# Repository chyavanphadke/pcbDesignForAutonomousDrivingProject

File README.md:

# pcbDesignForAutonomousDrivingProject

Schematic Diagram

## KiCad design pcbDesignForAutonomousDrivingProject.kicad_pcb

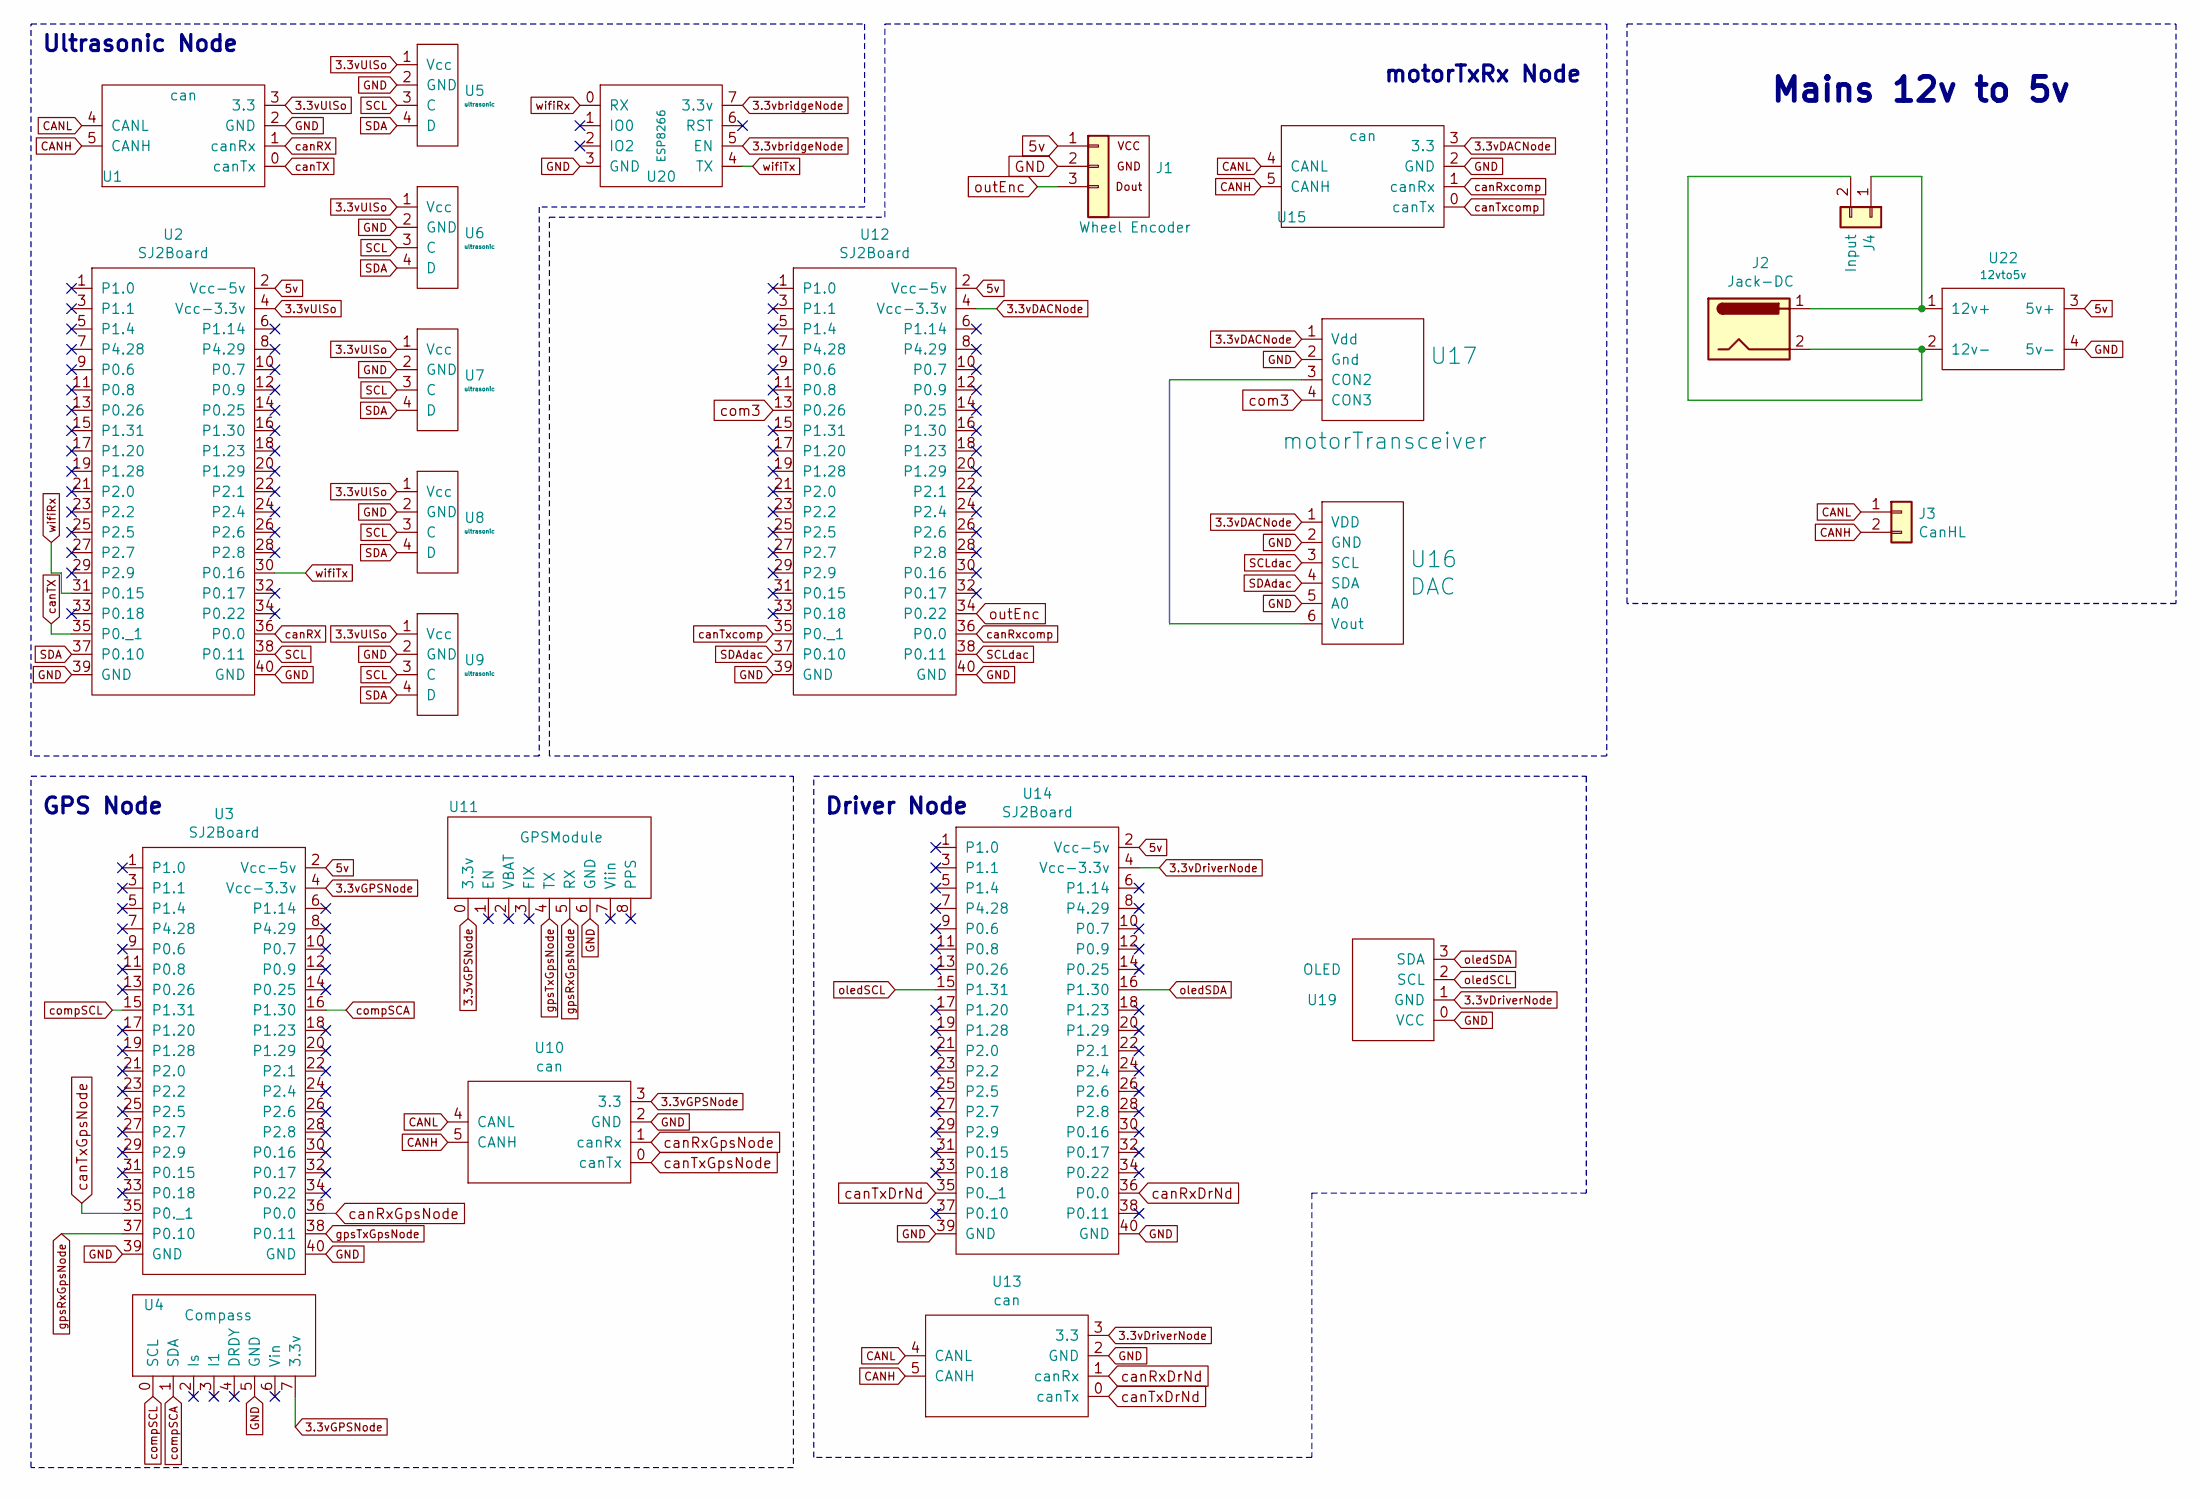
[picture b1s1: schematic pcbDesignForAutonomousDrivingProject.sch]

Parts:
J1: Wheel Encoder; WheelEncoder
J2: Jack-DC; BarrelJack_Horizontal
J3: CanHL; PinHeader_1x02_P2.54mm_Vertical
J4: Input; PinHeader_1x02_P2.54mm_Vertical
U1, U10, U13, U15: can
U2, U3, U12, U14: SJ2Board; sj2Board
U4: Compass; compass
U5, U6, U7, U8, U9: ultrasonic
U11: GPSModule; GPS
U16: DAC
U17: motorTransceiver
U19: OLED; Oled
U20: ESP8266
U22: 12vto5v

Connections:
3.3vDACNode: U12.4 (Vcc-3.3v), U15.3 (3.3), U16.1 (VDD), U17.1 (Vdd)
3.3vDriverNode: U13.3 (3.3), U14.4 (Vcc-3.3v), U19.1 (GND)
3.3vGPSNode: U3.4 (Vcc-3.3v), U4.7 (3.3v), U10.3 (3.3), U11.0 (3.3v)
3.3vUlSo: U1.3 (3.3), U2.4 (Vcc-3.3v), U5.1 (Vcc), U6.1 (Vcc), U7.1 (Vcc), U8.1 (Vcc), U9.1 (Vcc)
3.3vbridgeNode: U20.5 (EN), U20.7 (3.3v)
5v: J1.1 (VCC), U2.2 (Vcc-5v), U3.2 (Vcc-5v), U12.2 (Vcc-5v), U14.2 (Vcc-5v), U22.3 (5v+)
CANH: J3.2, U1.5 (CANH), U10.5 (CANH), U13.5 (CANH), U15.5 (CANH)
CANL: J3.1, U1.4 (CANL), U10.4 (CANL), U13.4 (CANL), U15.4 (CANL)
GND: J1.2 (GND), U1.2 (GND), U2.39 (GND), U2.40 (GND), U3.39 (GND), U3.40 (GND), U4.5 (GND), U5.2 (GND), U6.2 (GND), U7.2 (GND), U8.2 (GND), U9.2 (GND), U10.2 (GND), U11.6 (GND), U12.39 (GND), U12.40 (GND), U13.2 (GND), U14.39 (GND), U14.40 (GND), U15.2 (GND), U16.2 (GND), U16.5 (A0), U17.2 (Gnd), U19.0 (VCC), U20.3 (GND), U22.4 (5v-)
unnamed: J2.1, J4.1, U22.1 (12v+)
unnamed: J2.2, J4.2, U22.2 (12v-)
unnamed: U16.6 (Vout), U17.3 (CON2)
SCL: U2.38 (P0.11), U5.3 (C), U6.3 (C), U7.3 (C), U8.3 (C), U9.3 (C)
SCLdac: U12.38 (P0.11), U16.3 (SCL)
SDA: U2.37 (P0.10), U5.4 (D), U6.4 (D), U7.4 (D), U8.4 (D), U9.4 (D)
SDAdac: U12.37 (P0.10), U16.4 (SDA)
canRX: U1.1 (canRx), U2.36 (P0.0)
canRxDrNd: U13.1 (canRx), U14.36 (P0.0)
canRxGpsNode: U3.36 (P0.0), U10.1 (canRx)
canRxcomp: U12.36 (P0.0), U15.1 (canRx)
canTX: U1.0 (canTx), U2.35 (P0._1)
canTxDrNd: U13.0 (canTx), U14.35 (P0._1)
canTxGpsNode: U3.35 (P0._1), U10.0 (canTx)
canTxcomp: U12.35 (P0._1), U15.0 (canTx)
com3: U12.13 (P0.26), U17.4 (CON3)
compSCA: U3.16 (P1.30), U4.1 (SDA)
compSCL: U3.15 (P1.31), U4.0 (SCL)
gpsRxGpsNode: U3.37 (P0.10), U11.5 (RX)
gpsTxGpsNode: U3.38 (P0.11), U11.4 (TX)
oledSCL: U14.15 (P1.31), U19.2 (SCL)
oledSDA: U14.16 (P1.30), U19.3 (SDA)
outEnc: J1.3 (D0), U12.34 (P0.22)
wifiRx: U2.31 (P0.15), U20.0 (RX)
wifiTx: U2.30 (P0.16), U20.4 (TX)

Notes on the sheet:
GPS Node
Driver Node
Ultrasonic Node
motorTxRx Node
Mains 12v to 5v

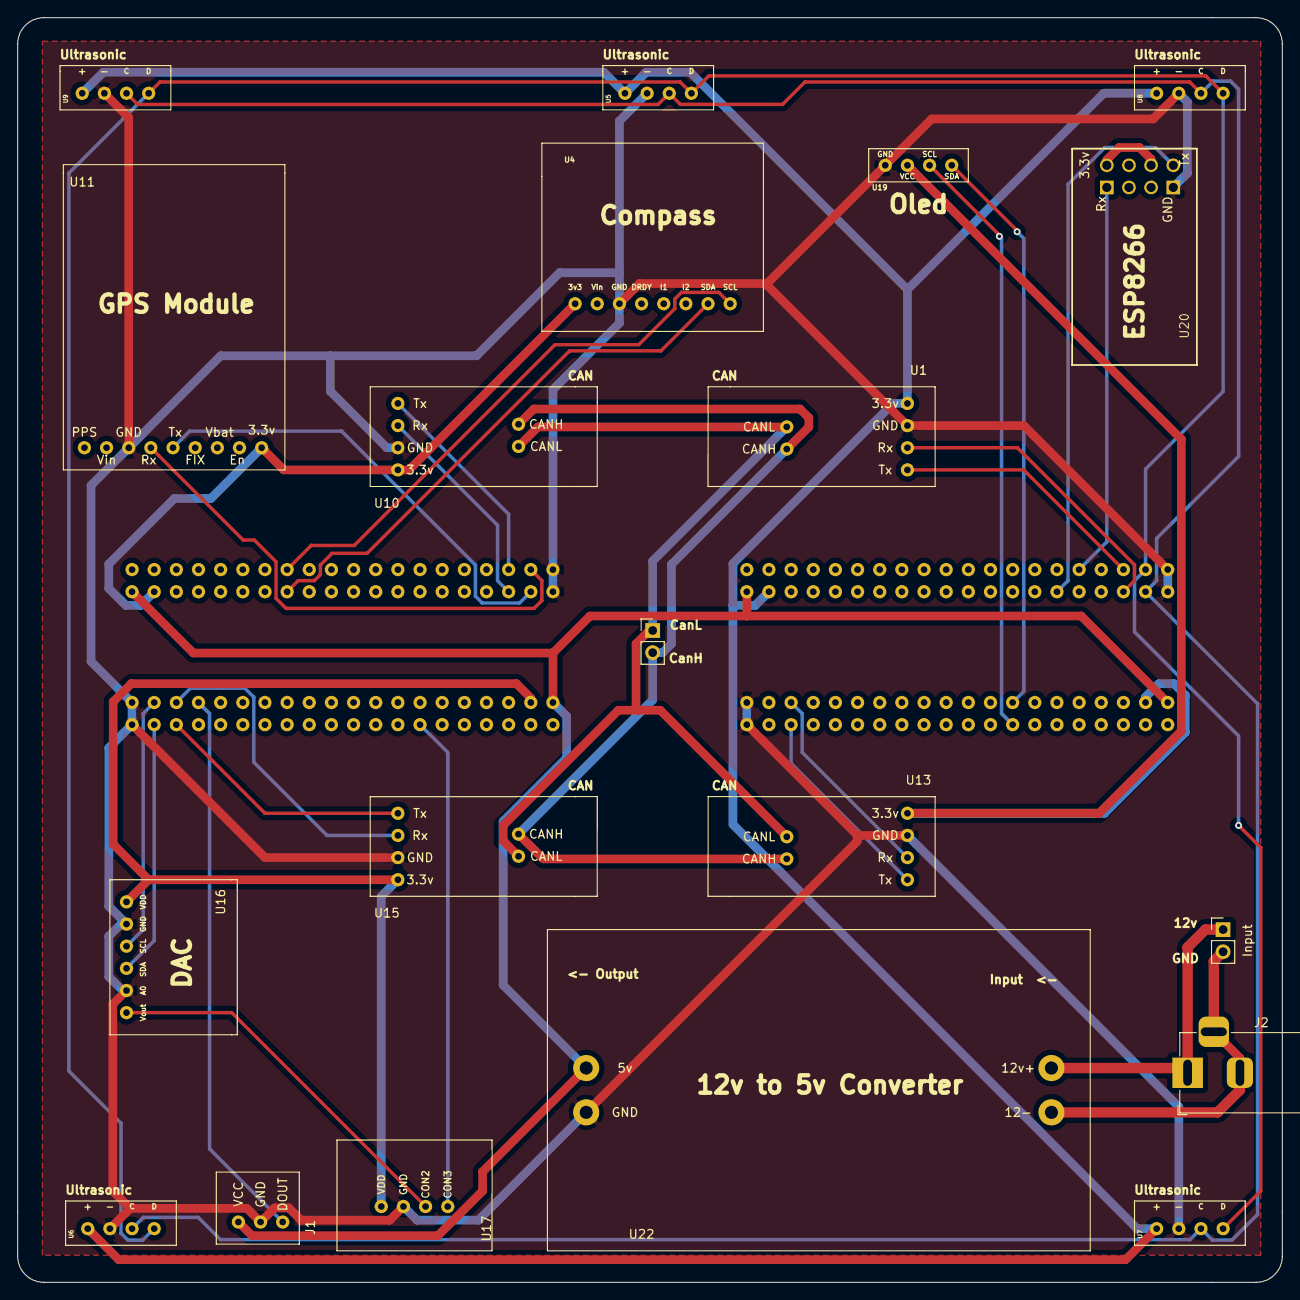
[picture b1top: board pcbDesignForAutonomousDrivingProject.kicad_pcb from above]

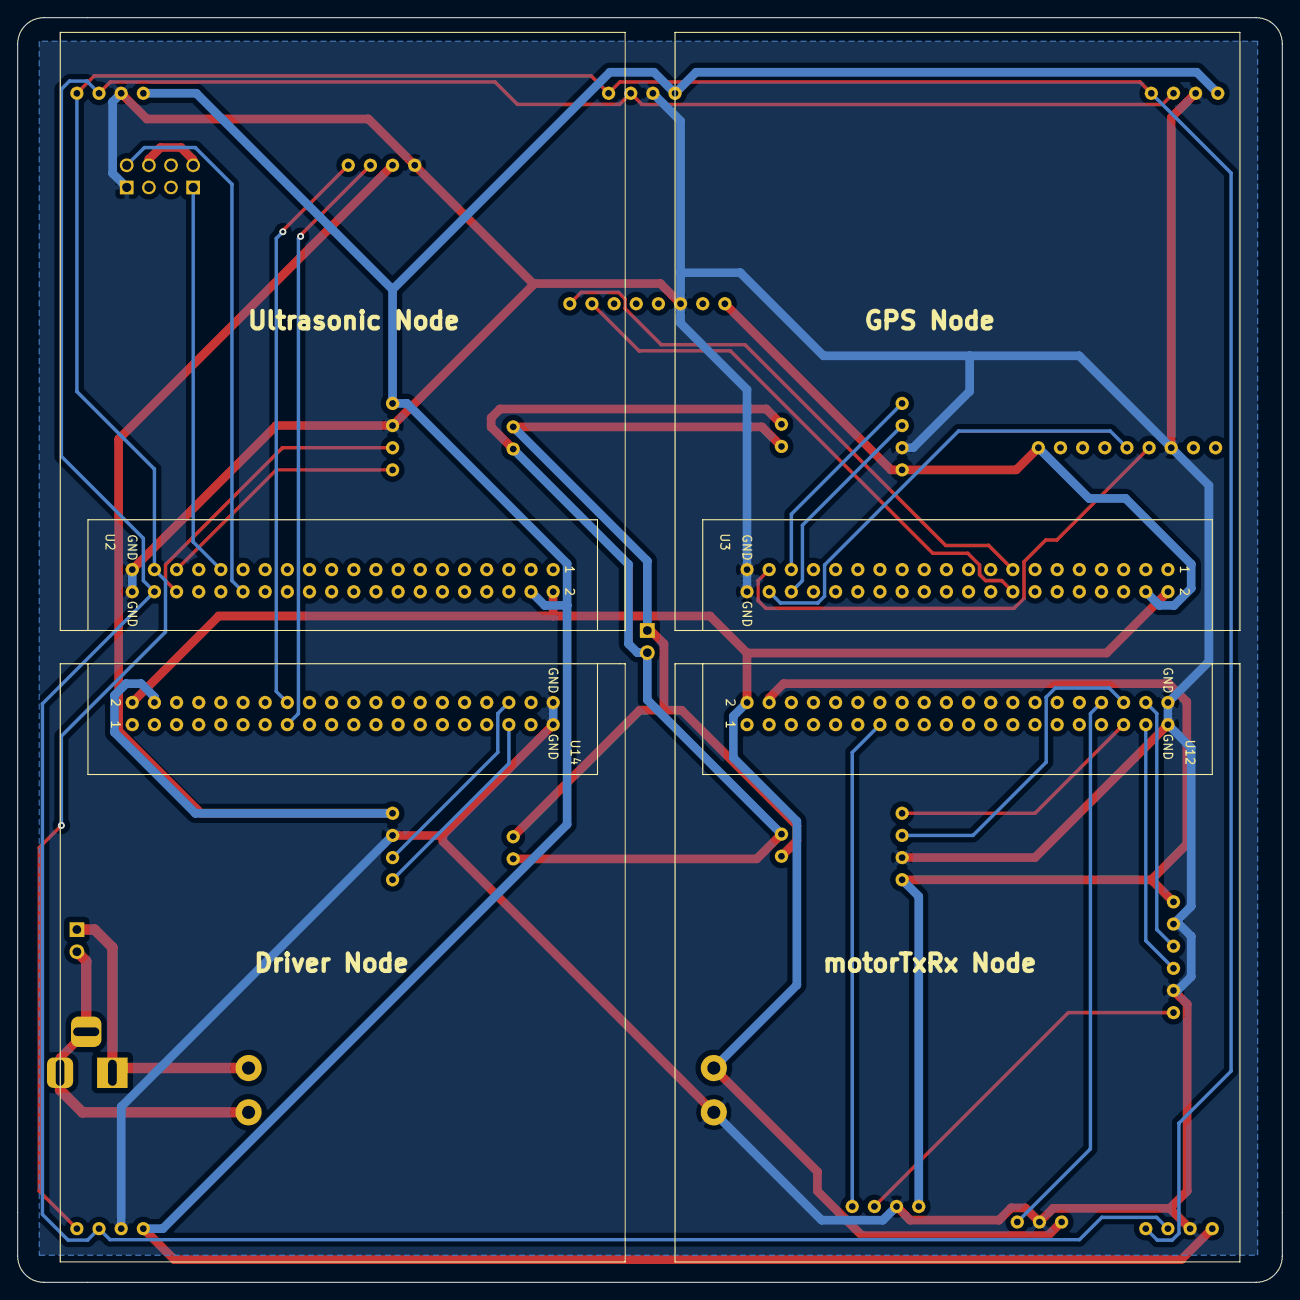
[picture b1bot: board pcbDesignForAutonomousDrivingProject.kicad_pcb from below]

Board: 2 copper layers, 145.0 x 145.0 mm, 24 parts (4 on the bottom side), 34 nets.

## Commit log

2021-04-17 Commit Made on - April 16th 2021 @ 06:18:07 PM
2021-04-17 Commit Made on - April 16th 2021 @ 06:48:49 PM
2021-04-17 Commit Made on - April 16th 2021 @ 07:11:48 PM
2021-04-17 Commit Made on - April 17th 2021 @ 01:57:31 PM
2021-04-18 Commit Made on - April 18th 2021 @ 12:32:16 PM
2021-04-18 Commit Made on - April 18th 2021 @ 03:43:33 PM
2021-04-18 Commit Made on - April 18th 2021 @ 03:44:38 PM
2021-04-18 Commit Made on - April 18th 2021 @ 04:05:23 PM
2021-04-22 Commit Made on - April 22th 2021 @ :52:41
2021-04-22 Commit Made on - April 22th 2021 @ :56:29
2021-04-22 Commit Made on - April 22th 2021 @ :57:10
2021-04-22 schematic image
2021-04-22 Commit Made on - April 22th 2021 @ 11:12:07 AM
2021-04-22 Commit Made on - April 22th 2021 @ 03:50:36 PM
2021-04-23 Commit Made on - April 22th 2021 @ 08:30:16 PM
2021-04-23 Commit Made on - April 22th 2021 @ 08:38:03 PM
2021-04-24 Commit Made on - April 23th 2021 @ 08:27:51 PM
2021-04-24 Commit Made on - April 23th 2021 @ 11:15:02 PM
2021-04-25 Commit Made on - April 25th 2021 @ 03:14:31 PM
2021-04-26 Commit Made on - April 25th 2021 @ 11:22:35 PM
2021-04-26 Layout Version One completed here
    Next will be routing
2021-04-26 <<<<<<<<<<<<<<< Layout Version One completed here >>>>>>>>>>>>>>
2021-04-27 Commit Made on - April 27th 2021 @ 10:05:10 AM
2021-04-27 Commit Made on - April 27th 2021 @ 10:09:59 AM
2021-04-27 Commit Made on - April 27th 2021 @ 01:52:08 PM
2021-04-29 Commit Made on - April 28th 2021 @ 11:39:06 PM
2021-04-29 Commit Made on - April 29th 2021 @ :36:51
2021-04-29 Commit Made on - April 29th 2021 @ :52:21
2021-04-29 Commit Made on - April 29th 2021 @ :53:10
2021-04-29 milestone 1
2021-04-29 Commit Made on - April 29th 2021 @ :33:39
2021-04-29 Commit Made on - April 29th 2021 @ :33:49
2021-04-29 Commit Made on - April 29th 2021 @ :40:18
2021-04-29 Commit Made on - April 29th 2021 @ :41:47
2021-04-29 Commit Made on - April 29th 2021 @ 10:42:38 AM
2021-04-29 Commit Made on - April 29th 2021 @ 12:56:31 PM
2021-04-29 Commit Made on - April 29th 2021 @ 12:56:50 PM
2021-04-29 Commit Made on - April 29th 2021 @ 12:58:59 PM
2021-04-29 Commit Made on - April 29th 2021 @ 03:11:24 PM
2021-05-16 Commit Made on - May 15th 2021 @ 05:40:51 PM
